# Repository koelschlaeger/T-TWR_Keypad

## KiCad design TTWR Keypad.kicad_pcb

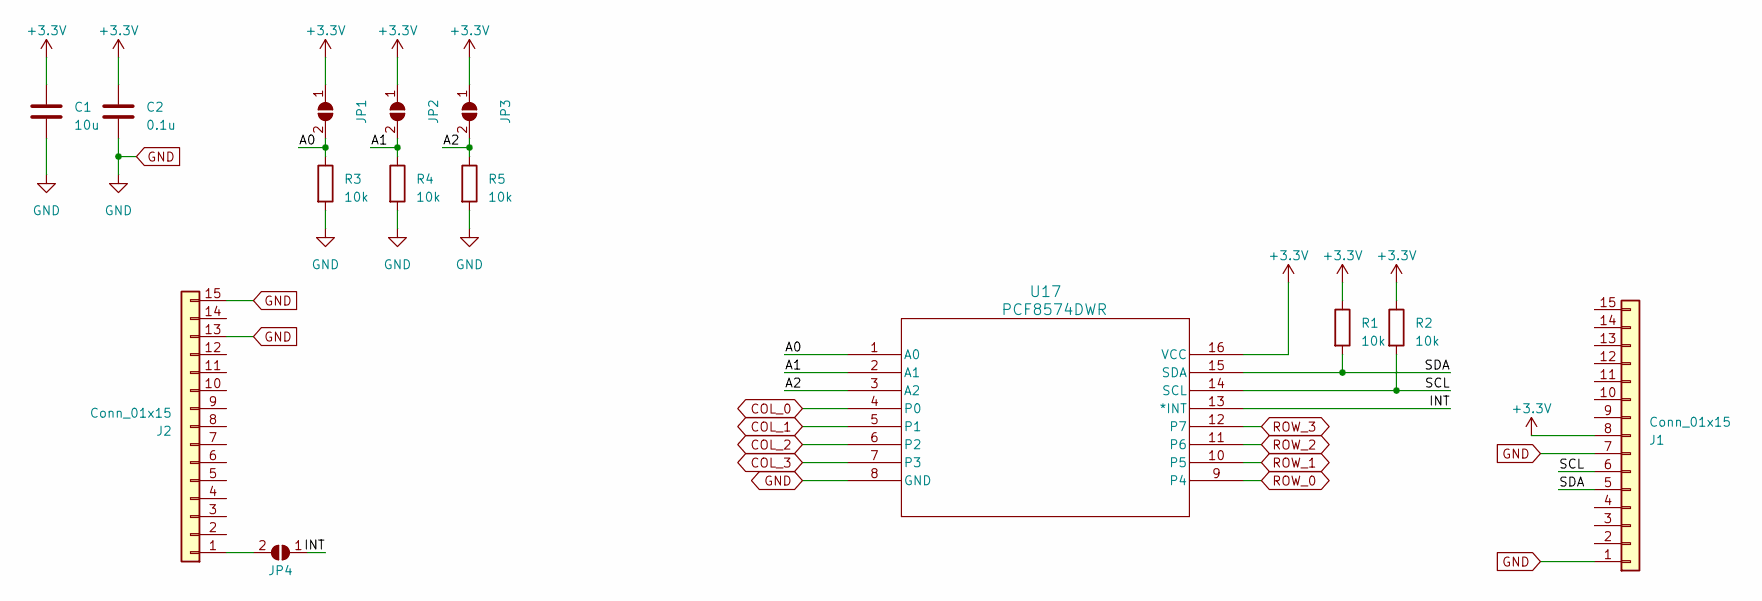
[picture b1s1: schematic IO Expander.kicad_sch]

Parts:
C1: 10u; C_0603_1608Metric_Pad1.08x0.95mm_HandSolder
C2: 0.1u; C_0603_1608Metric_Pad1.08x0.95mm_HandSolder
J1, J2: Conn_01x15; PinHeader_1x15_P1.00mm_Vertical
JP1, JP2, JP3, JP4: SolderJumper_2_Open; SolderJumper-2_P1.3mm_Open_RoundedPad1.0x1.5mm
R1, R2, R3, R4, R5: 10k; R_0603_1608Metric_Pad0.98x0.95mm_HandSolder
U17: PCF8574DWR; SOT162-1_NXP-M

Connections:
+3.3V: C1.1, C2.1, J1.8, JP1.1 (A), JP2.1 (A), JP3.1 (A), R1.1, R2.1, U17.16 (VCC)
/IO Expander/A0: JP1.2 (B), R3.1, U17.1 (A0)
/IO Expander/A1: JP2.2 (B), R4.1, U17.2 (A1)
/IO Expander/A2: JP3.2 (B), R5.1, U17.3 (A2)
/IO Expander/INT: JP4.1 (A), U17.13 (*INT)
/IO Expander/SCL: J1.6, R2.2, U17.14 (SCL)
/IO Expander/SDA: J1.5, R1.2, U17.15 (SDA)
COL_0: U17.4 (P0); also elsewhere on the board
COL_1: U17.5 (P1); also elsewhere on the board
COL_2: U17.6 (P2); also elsewhere on the board
COL_3: U17.7 (P3); also elsewhere on the board
GND: C1.2, C2.2, J1.1, J1.7, J2.13, J2.15, R3.2, R4.2, R5.2, U17.8 (GND)
unnamed: J2.1, JP4.2 (B)
ROW_0: U17.9 (P4); also elsewhere on the board
ROW_1: U17.10 (P5); also elsewhere on the board
ROW_2: U17.11 (P6); also elsewhere on the board
ROW_3: U17.12 (P7); also elsewhere on the board

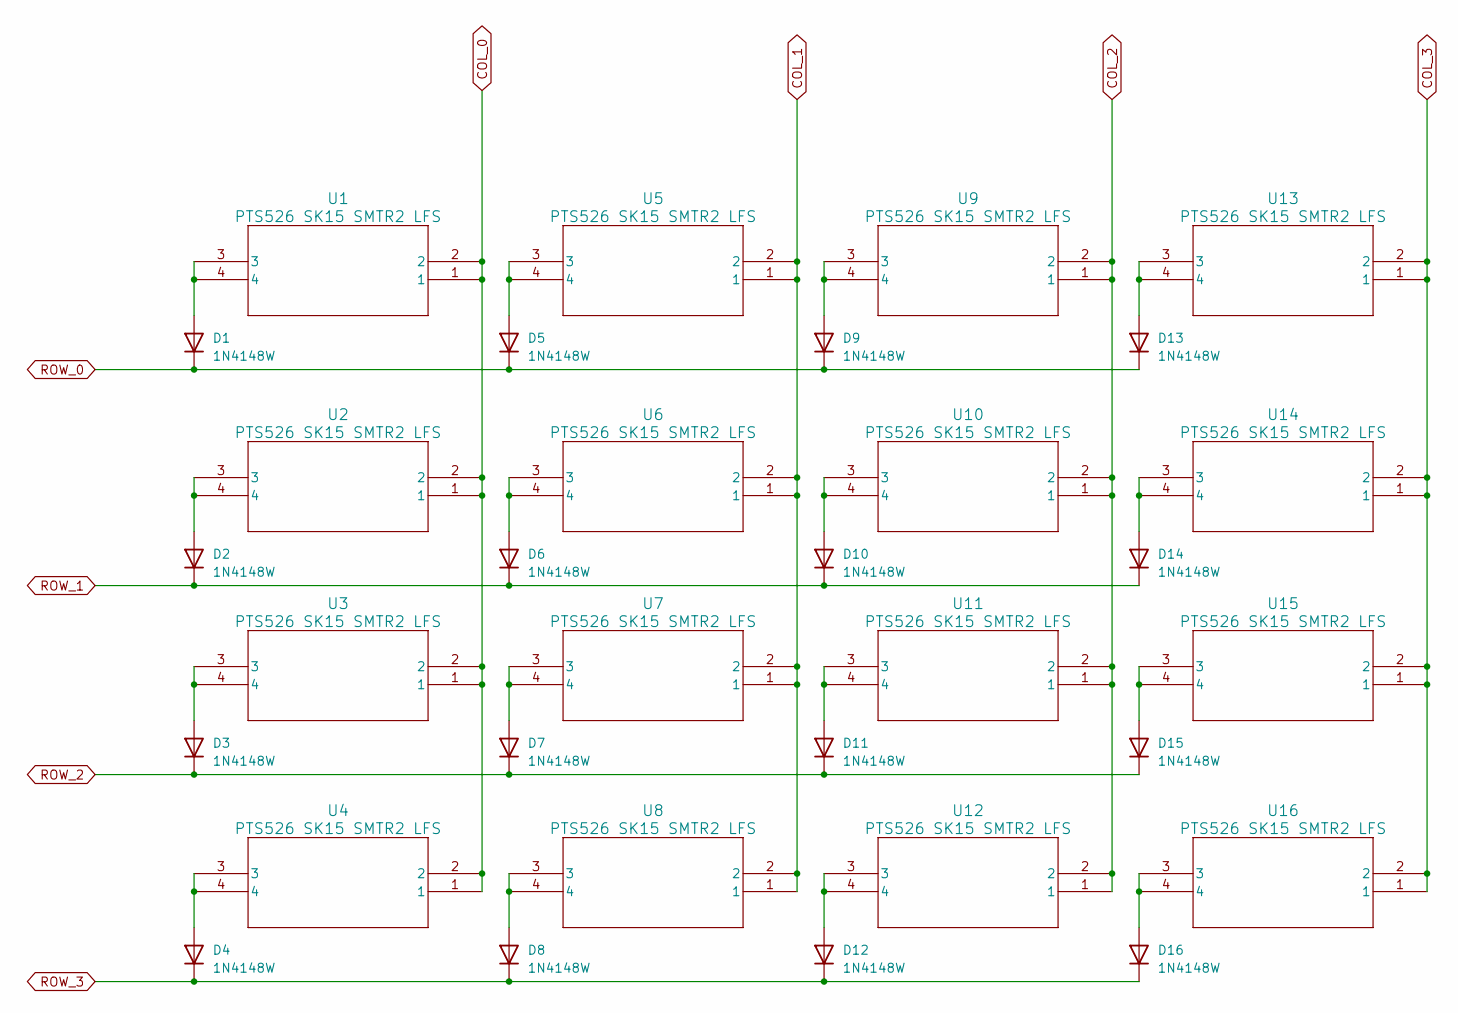
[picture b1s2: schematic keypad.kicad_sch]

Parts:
D1, D2, D3, D4, D5, D6, D7, D8, D9, D10, D11, D12, D13, D14, D15, D16: 1N4148W; D_SOD-123
U1, U2, U3, U4, U5, U6, U7, U8, U9, U10, U11, U12, U13, U14, U15, U16: PTS526 SK15 SMTR2 LFS; PTS526_SK15_SMTR2_LFS

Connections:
COL_0: U1.1, U1.2, U2.1, U2.2, U3.1, U3.2, U4.1, U4.2; also elsewhere on the board
COL_1: U5.1, U5.2, U6.1, U6.2, U7.1, U7.2, U8.1, U8.2; also elsewhere on the board
COL_2: U9.1, U9.2, U10.1, U10.2, U11.1, U11.2, U12.1, U12.2; also elsewhere on the board
COL_3: U13.1, U13.2, U14.1, U14.2, U15.1, U15.2, U16.1, U16.2; also elsewhere on the board
unnamed: D1.2 (A), U1.3, U1.4
unnamed: D2.2 (A), U2.3, U2.4
unnamed: D3.2 (A), U3.3, U3.4
unnamed: D4.2 (A), U4.3, U4.4
unnamed: D5.2 (A), U5.3, U5.4
unnamed: D6.2 (A), U6.3, U6.4
unnamed: D7.2 (A), U7.3, U7.4
unnamed: D8.2 (A), U8.3, U8.4
unnamed: D9.2 (A), U9.3, U9.4
unnamed: D10.2 (A), U10.3, U10.4
unnamed: D11.2 (A), U11.3, U11.4
unnamed: D12.2 (A), U12.3, U12.4
unnamed: D13.2 (A), U13.3, U13.4
unnamed: D14.2 (A), U14.3, U14.4
unnamed: D15.2 (A), U15.3, U15.4
unnamed: D16.2 (A), U16.3, U16.4
ROW_0: D1.1 (K), D5.1 (K), D9.1 (K), D13.1 (K); also elsewhere on the board
ROW_1: D2.1 (K), D6.1 (K), D10.1 (K), D14.1 (K); also elsewhere on the board
ROW_2: D3.1 (K), D7.1 (K), D11.1 (K), D15.1 (K); also elsewhere on the board
ROW_3: D4.1 (K), D8.1 (K), D12.1 (K), D16.1 (K); also elsewhere on the board

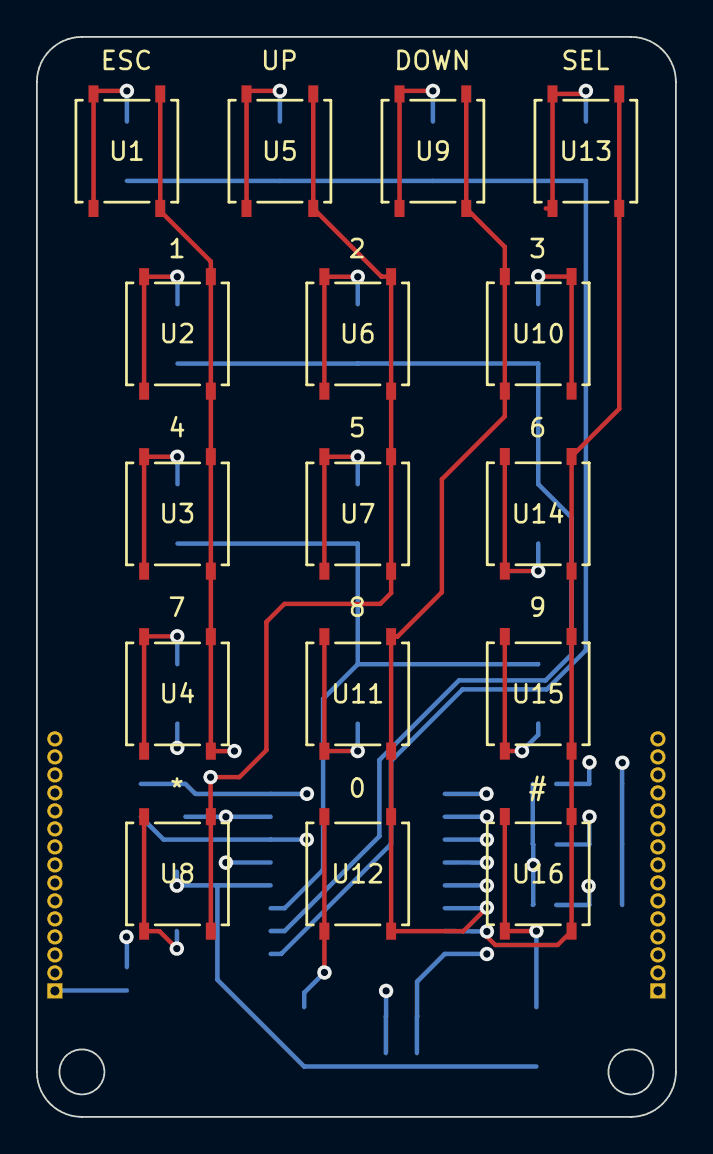
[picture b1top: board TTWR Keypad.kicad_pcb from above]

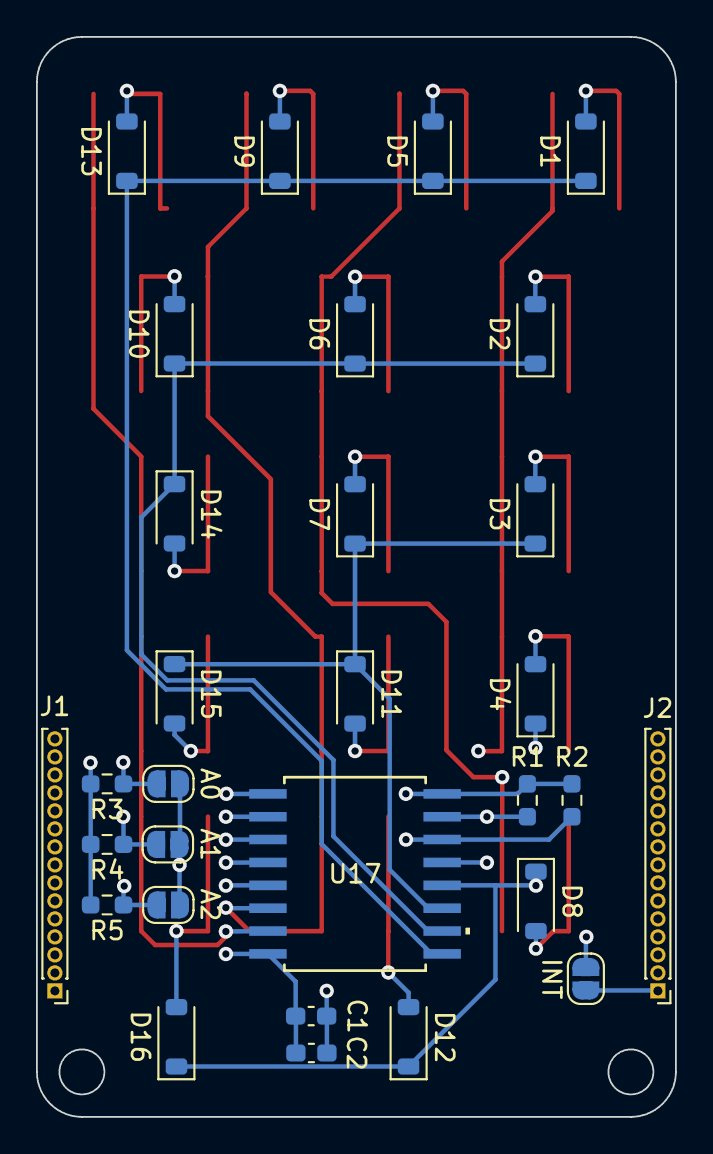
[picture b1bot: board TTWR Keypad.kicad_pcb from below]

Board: 4 copper layers, 35.5 x 60.0 mm, 46 parts (30 on the bottom side), 33 nets.

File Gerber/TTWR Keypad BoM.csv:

"Reference","Value","Datasheet","Footprint","Qty","DNP"
"C1","10u","https://search.murata.co.jp/Ceramy/image/img/A01X/G101/ENG/G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","Capacitor_SMD:C_0603_1608Metric_Pad1.08x0.95mm_HandSolder","1",""
"C2","0.1u","https://www.we-online.com/components/products/datasheet/8850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","Capacitor_SMD:C_0603_1608Metric_Pad1.08x0.95mm_HandSolder","1",""
"D1,D2,D3,D4,D5,D6,D7,D8,D9,D10,D11,D12,D13,D14,D15,D16","1N4148W","https://www.vishay.com/docs/85748/1n4148w.pdf","Diode_SMD:D_SOD-123","16",""
"JP1,JP2,JP3,JP4","SolderJumper_2_Open","~","Jumper:SolderJumper-2_P1.3mm_Open_RoundedPad1.0x1.5mm","4",""
"R1,R2,R3,R4,R5","10k","https://www.vishay.com/docs/20066/rcce3.pdf","Resistor_SMD:R_0603_1608Metric_Pad0.98x0.95mm_HandSolder","5",""
"U1,U2,U3,U4,U5,U6,U7,U8,U9,U10,U11,U12,U13,U14,U15,U16","PTS526 SK15 SMTR2 LFS","https://www.ckswitches.com/media/2780/pts526.pdf","footprints:PTS526_SK15_SMTR2_LFS","16",""
"U17","PCF8574DWR","https://www.nxp.com/docs/en/data-sheet/PCF8574_PCF8574A.pdf","footprints:SOT162-1_NXP-M","1",""

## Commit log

2024-03-25 Rev 1. New layout on 4 layer board. Changed package/footprint of the IO Expander to SOP-16.
2024-03-25 Added solid model for switches
2024-03-27 removed zip filter from .gitignore
2024-03-27 Changed footprints of R* and C* to 0603 and made layout adjustments to compensate. Added JLCPCB metafiles for fab and population.
2024-03-29 Added labels for switches. Changed jumper labels to functional labels.
2024-04-13 Added ground plane to second inner layer and regenerated gerber files.

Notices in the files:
TTWR Keypad.kicad_pcb:
License: CC BY 4.0
